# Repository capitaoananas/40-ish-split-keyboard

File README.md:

# Split-Keyboard-PCB
A 40% ish reversible split keyboard inspired by the [MiniDox](https://github.com/That-Canadian/MiniDox_PCB) keyboard

## PCB

Here's my PCB! It was made in KiCad..

### Schematic

### PCB

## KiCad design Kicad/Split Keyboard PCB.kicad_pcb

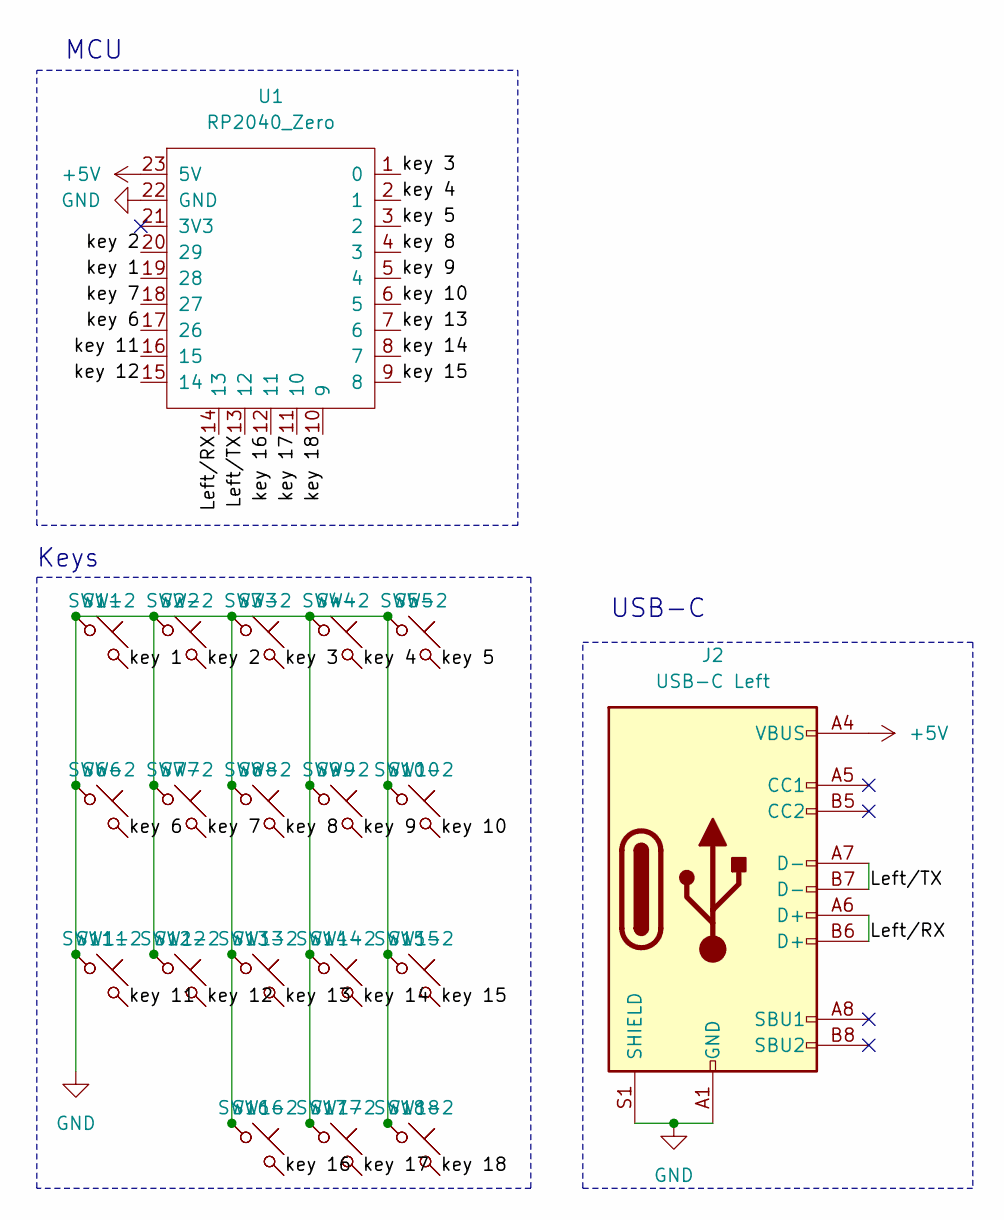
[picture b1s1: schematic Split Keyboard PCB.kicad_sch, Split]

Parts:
J2: USB-C Left; TYPE-C-31-M-13C
SW1, SW1-2, SW2, SW2-2, SW3, SW3-2, SW4, SW4-2, SW5, SW5-2, SW6, SW6-2, SW7, SW7-2, SW8, SW8-2, SW9, SW9-2, SW10, SW10-2, SW11, SW11-2, SW12, SW12-2, SW13, SW13-2, SW14, SW14-2, SW15, SW15-2, SW16, SW16-2, SW17, SW17-2: SW_Push_45deg; MX-Hotswap-1U
SW18, SW18-2: SW_Push_45deg; MX-Hotswap-1.5U
U1: RP2040_Zero

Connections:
+5V: J2.A4 (VBUS), J2.A9 (VBUS), J2.B4 (VBUS), J2.B9 (VBUS), U1.23 (5V)
/Left/RX: J2.A6 (D+), J2.B6 (D+), U1.14 (13)
/Left/TX: J2.A7 (D-), J2.B7 (D-), U1.13 (12)
/key 1: SW1.2, SW1-2.2, U1.19 (28)
/key 2: SW2.2, SW2-2.2, U1.20 (29)
/key 3: SW3.2, SW3-2.2, U1.1 (0)
/key 4: SW4.2, SW4-2.2, U1.2 (1)
/key 5: SW5.2, SW5-2.2, U1.3 (2)
/key 6: SW6.2, SW6-2.2, U1.17 (26)
/key 7: SW7.2, SW7-2.2, U1.18 (27)
/key 8: SW8.2, SW8-2.2, U1.4 (3)
/key 9: SW9.2, SW9-2.2, U1.5 (4)
/key 10: SW10.2, SW10-2.2, U1.6 (5)
/key 11: SW11.2, SW11-2.2, U1.16 (15)
/key 12: SW12.2, SW12-2.2, U1.15 (14)
/key 13: SW13.2, SW13-2.2, U1.7 (6)
/key 14: SW14.2, SW14-2.2, U1.8 (7)
/key 15: SW15.2, SW15-2.2, U1.9 (8)
/key 16: SW16.2, SW16-2.2, U1.12 (11)
/key 17: SW17.2, SW17-2.2, U1.11 (10)
/key 18: SW18.2, SW18-2.2, U1.10 (9)
GND: J2.A1 (GND), J2.A12 (GND), J2.B1 (GND), J2.B12 (GND), J2.S1 (SHIELD), SW1.1, SW1-2.1, SW2.1, SW2-2.1, SW3.1, SW3-2.1, SW4.1, SW4-2.1, SW5.1, SW5-2.1, SW6.1, SW6-2.1, SW7.1, SW7-2.1, SW8.1, SW8-2.1, SW9.1, SW9-2.1, SW10.1, SW10-2.1, SW11.1, SW11-2.1, SW12.1, SW12-2.1, SW13.1, SW13-2.1, SW14.1, SW14-2.1, SW15.1, SW15-2.1, SW16.1, SW16-2.1, SW17.1, SW17-2.1, SW18.1, SW18-2.1, U1.22 (GND)

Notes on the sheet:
USB-C
Keys
MCU

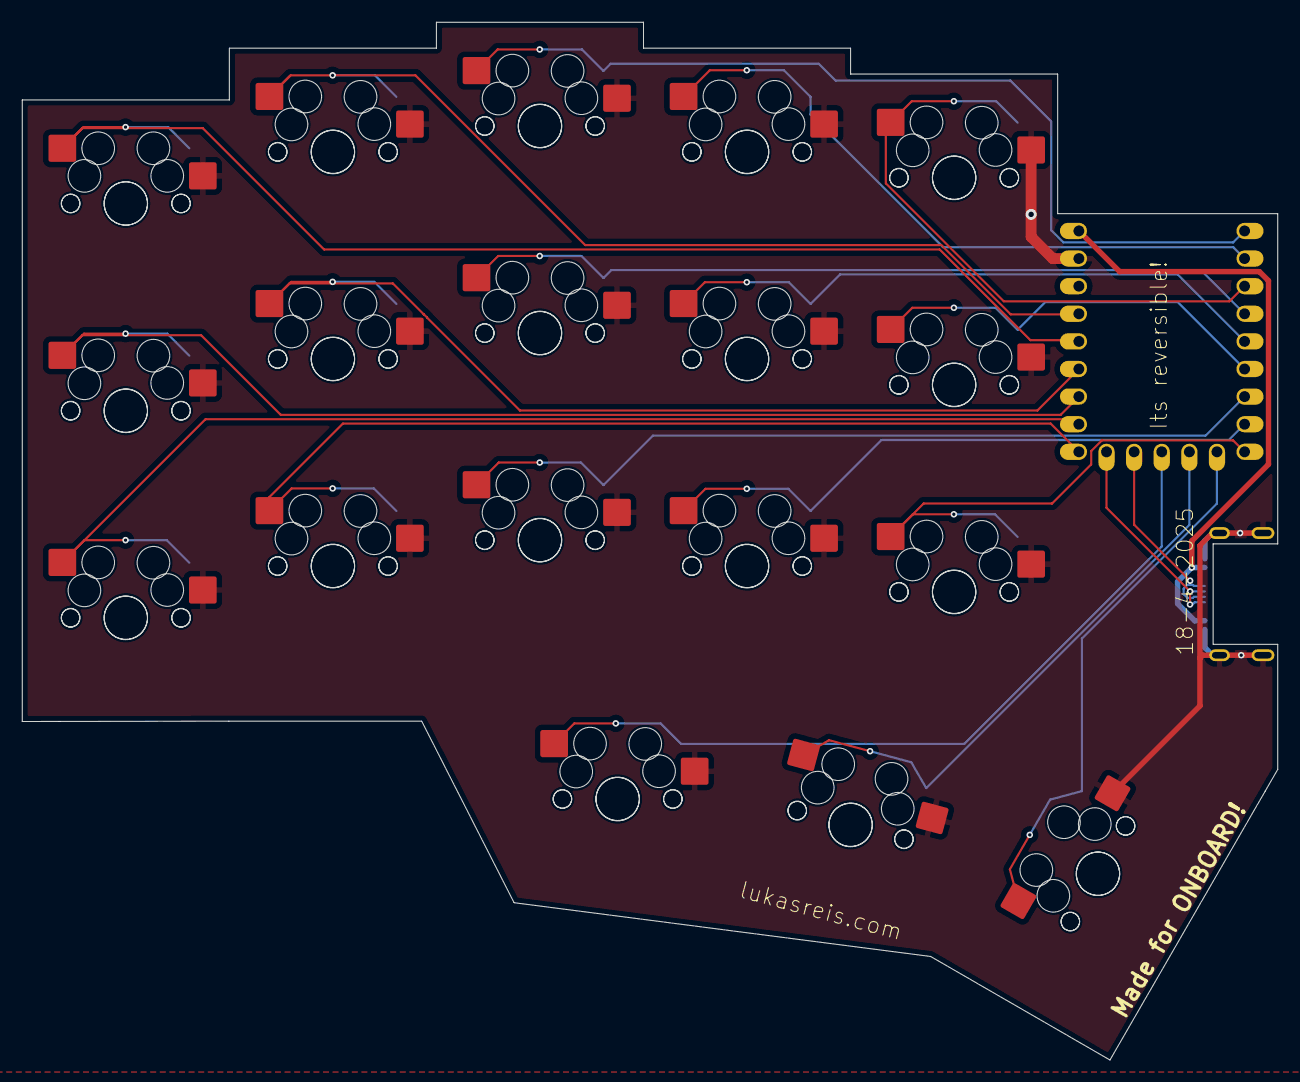
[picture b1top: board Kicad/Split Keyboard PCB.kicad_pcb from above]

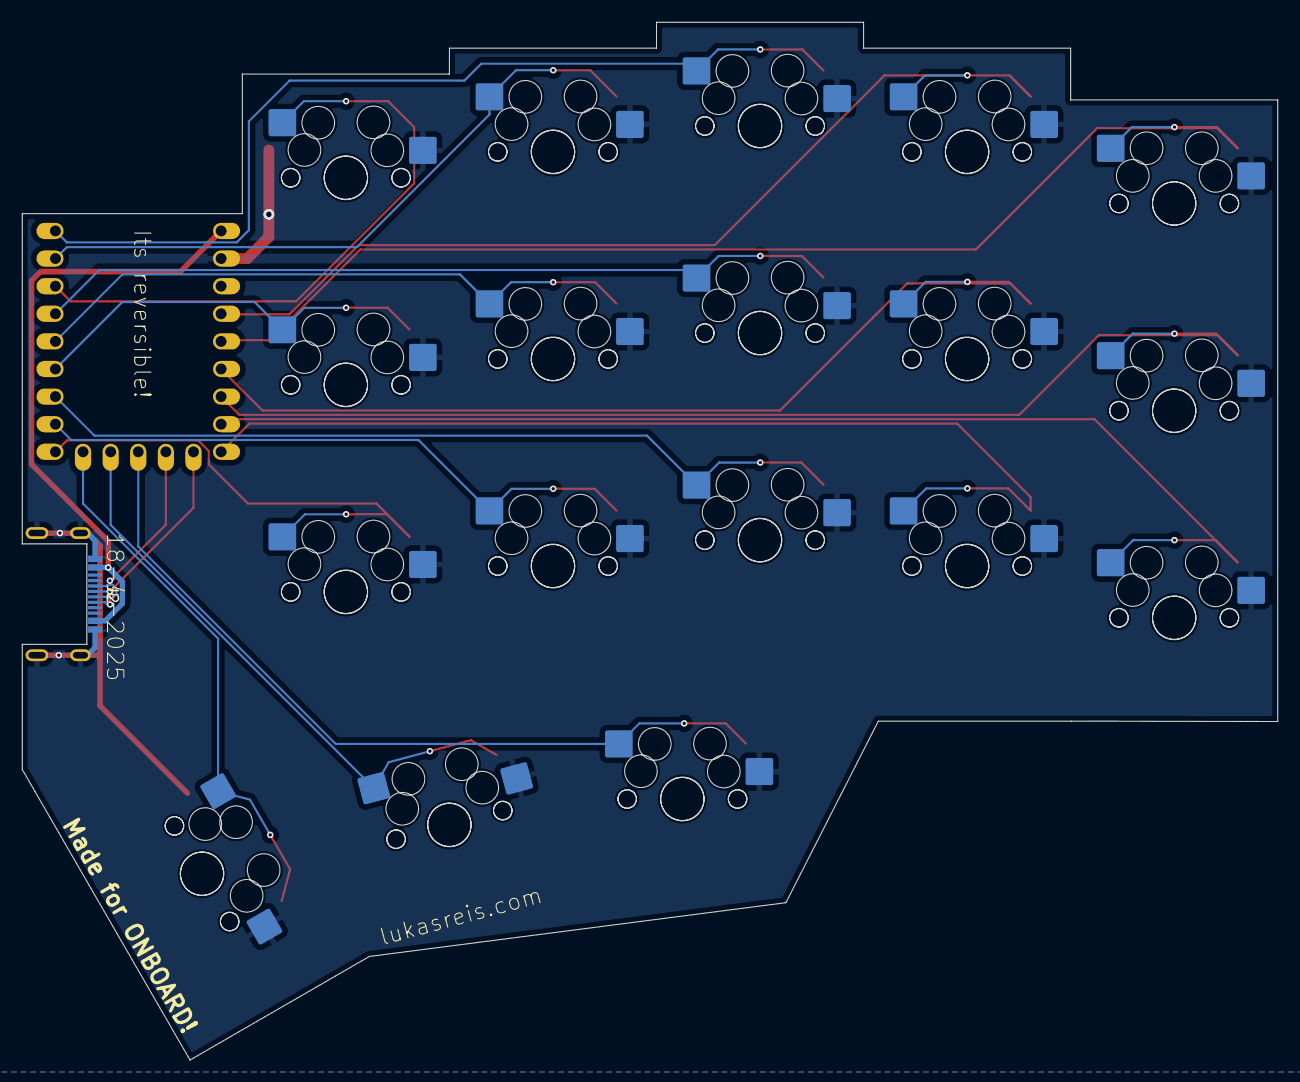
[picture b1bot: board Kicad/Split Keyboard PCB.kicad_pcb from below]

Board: 2 copper layers, 115.5 x 95.5 mm, 38 parts (19 on the bottom side), 22 nets.

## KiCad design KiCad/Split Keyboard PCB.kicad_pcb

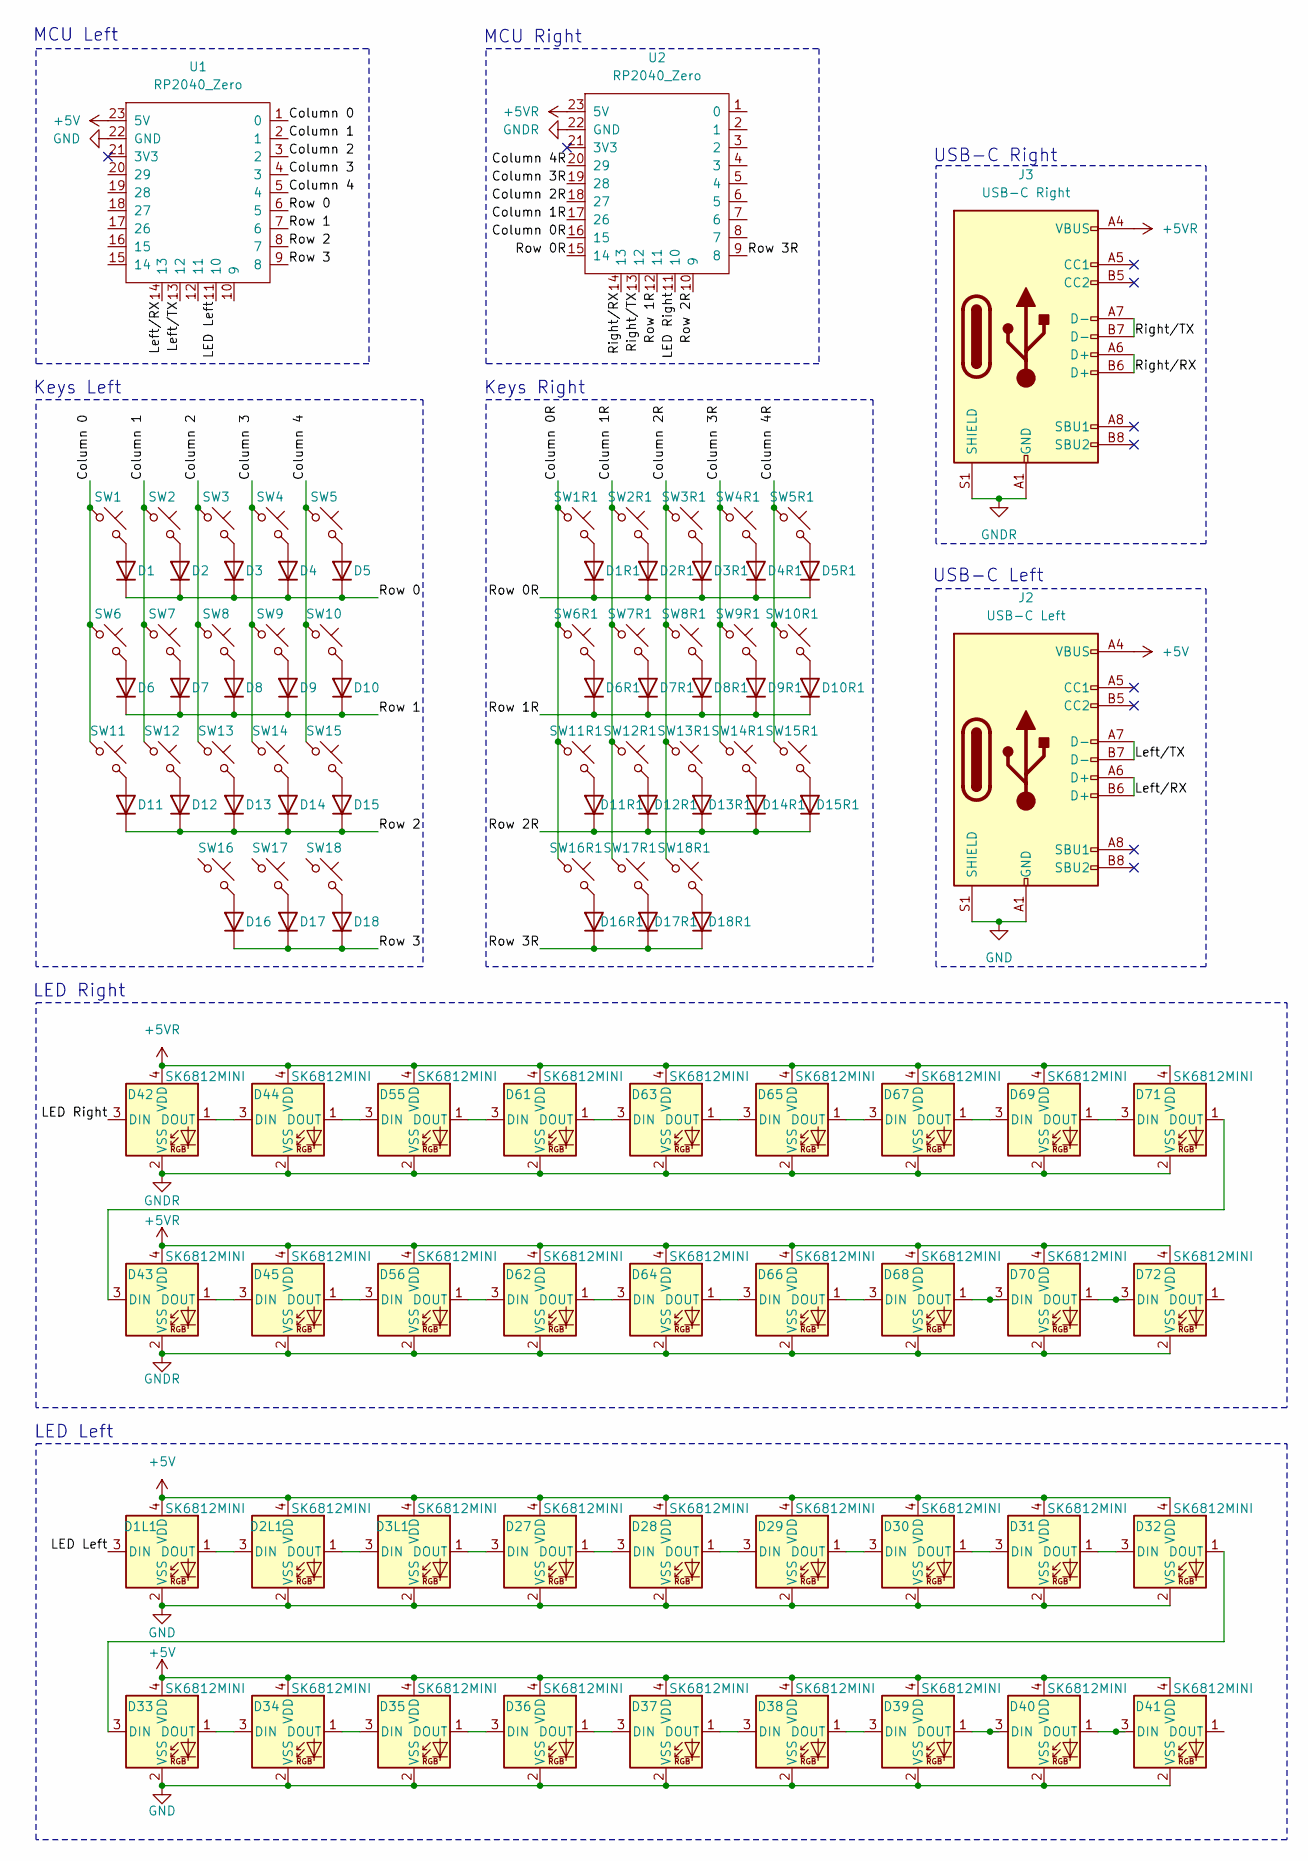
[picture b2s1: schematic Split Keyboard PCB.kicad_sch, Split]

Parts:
D1, D1R1, D2, D2R1, D3, D3R1, D4, D4R1, D5, D5R1, D6, D6R1, D7, D7R1, D8, D8R1, D9, D9R1, D10, D10R1, D11, D11R1, D12, D12R1, D13, D13R1, D14, D14R1, D15, D15R1, D16, D16R1, D17, D17R1, D18, D18R1: D; Diode_SOD-123
D1L1, D2L1, D3L1, D27, D28, D29, D30, D31, D32, D33, D34, D35, D36, D37, D38, D39, D40, D41, D42, D43, D44, D45, D55, D56, D61, D62, D63, D64, D65, D66, D67, D68, D69, D70, D71, D72: SK6812MINI; LED_SK6812MINI
J2: USB-C Left; TYPE-C-31-M-13C
J3: USB-C Right; TYPE-C-31-M-13C
SW1, SW1R1, SW2, SW2R1, SW3, SW3R1, SW4, SW4R1, SW5, SW5R1, SW6, SW6R1, SW7, SW7R1, SW8, SW8R1, SW9, SW9R1, SW10, SW10R1, SW11, SW11R1, SW12, SW12R1, SW13, SW13R1, SW14, SW14R1, SW15, SW15R1, SW16, SW17, SW17R1, SW18R1: SW_Push_45deg; MX-Hotswap-1U
SW16R1, SW18: SW_Push_45deg; MX-Hotswap-1.5U
U1, U2: RP2040_Zero

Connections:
+5V: D1L1.4 (VDD), D2L1.4 (VDD), D3L1.4 (VDD), D27.4 (VDD), D28.4 (VDD), D29.4 (VDD), D30.4 (VDD), D31.4 (VDD), D32.4 (VDD), D33.4 (VDD), D34.4 (VDD), D35.4 (VDD), D36.4 (VDD), D37.4 (VDD), D38.4 (VDD), D39.4 (VDD), D40.4 (VDD), D41.4 (VDD), J2.A4 (VBUS), J2.A9 (VBUS), J2.B4 (VBUS), J2.B9 (VBUS), U1.23 (5V)
+5VR: D42.4 (VDD), D43.4 (VDD), D44.4 (VDD), D45.4 (VDD), D55.4 (VDD), D56.4 (VDD), D61.4 (VDD), D62.4 (VDD), D63.4 (VDD), D64.4 (VDD), D65.4 (VDD), D66.4 (VDD), D67.4 (VDD), D68.4 (VDD), D69.4 (VDD), D70.4 (VDD), D71.4 (VDD), D72.4 (VDD), J3.A4 (VBUS), J3.A9 (VBUS), J3.B4 (VBUS), J3.B9 (VBUS), U2.23 (5V)
/Column 0: SW1.1, SW6.1, SW11.1, U1.1 (0)
/Column 0R: SW1R1.1, SW6R1.1, SW11R1.1, SW16R1.1, U2.16 (15)
/Column 1: SW2.1, SW7.1, SW12.1, U1.2 (1)
/Column 1R: SW2R1.1, SW7R1.1, SW12R1.1, SW17R1.1, U2.17 (26)
/Column 2: SW3.1, SW8.1, SW13.1, SW16.1, U1.3 (2)
/Column 2R: SW3R1.1, SW8R1.1, SW13R1.1, SW18R1.1, U2.18 (27)
/Column 3: SW4.1, SW9.1, SW14.1, SW17.1, U1.4 (3)
/Column 3R: SW4R1.1, SW9R1.1, SW14R1.1, U2.19 (28)
/Column 4: SW5.1, SW10.1, SW15.1, SW18.1, U1.5 (4)
/Column 4R: SW5R1.1, SW10R1.1, SW15R1.1, U2.20 (29)
/LED Left: D1L1.3 (DIN), U1.11 (10)
/LED Right: D42.3 (DIN), U2.11 (10)
/Left/RX: J2.A6 (D+), J2.B6 (D+), U1.14 (13)
/Left/TX: J2.A7 (D-), J2.B7 (D-), U1.13 (12)
/Right/RX: J3.A6 (D+), J3.B6 (D+), U2.14 (13)
/Right/TX: J3.A7 (D-), J3.B7 (D-), U2.13 (12)
/Row 0: D1.1 (K), D2.1 (K), D3.1 (K), D4.1 (K), D5.1 (K), U1.6 (5)
/Row 0R: D1R1.1 (K), D2R1.1 (K), D3R1.1 (K), D4R1.1 (K), D5R1.1 (K), U2.15 (14)
/Row 1: D6.1 (K), D7.1 (K), D8.1 (K), D9.1 (K), D10.1 (K), U1.7 (6)
/Row 1R: D6R1.1 (K), D7R1.1 (K), D8R1.1 (K), D9R1.1 (K), D10R1.1 (K), U2.12 (11)
/Row 2: D11.1 (K), D12.1 (K), D13.1 (K), D14.1 (K), D15.1 (K), U1.8 (7)
/Row 2R: D11R1.1 (K), D12R1.1 (K), D13R1.1 (K), D14R1.1 (K), D15R1.1 (K), U2.10 (9)
/Row 3: D16.1 (K), D17.1 (K), D18.1 (K), U1.9 (8)
/Row 3R: D16R1.1 (K), D17R1.1 (K), D18R1.1 (K), U2.9 (8)
GND: D1L1.2 (VSS), D2L1.2 (VSS), D3L1.2 (VSS), D27.2 (VSS), D28.2 (VSS), D29.2 (VSS), D30.2 (VSS), D31.2 (VSS), D32.2 (VSS), D33.2 (VSS), D34.2 (VSS), D35.2 (VSS), D36.2 (VSS), D37.2 (VSS), D38.2 (VSS), D39.2 (VSS), D40.2 (VSS), D41.2 (VSS), J2.A1 (GND), J2.A12 (GND), J2.B1 (GND), J2.B12 (GND), J2.S1 (SHIELD), U1.22 (GND)
GNDR: D42.2 (VSS), D43.2 (VSS), D44.2 (VSS), D45.2 (VSS), D55.2 (VSS), D56.2 (VSS), D61.2 (VSS), D62.2 (VSS), D63.2 (VSS), D64.2 (VSS), D65.2 (VSS), D66.2 (VSS), D67.2 (VSS), D68.2 (VSS), D69.2 (VSS), D70.2 (VSS), D71.2 (VSS), D72.2 (VSS), J3.A1 (GND), J3.A12 (GND), J3.B1 (GND), J3.B12 (GND), J3.S1 (SHIELD), U2.22 (GND)
unnamed: D1.2 (A), SW1.2
unnamed: D1L1.1 (DOUT), D2L1.3 (DIN)
unnamed: D1R1.2 (A), SW1R1.2
unnamed: D2.2 (A), SW2.2
unnamed: D2L1.1 (DOUT), D3L1.3 (DIN)
unnamed: D2R1.2 (A), SW2R1.2
unnamed: D3.2 (A), SW3.2
unnamed: D3R1.2 (A), SW3R1.2
unnamed: D4.2 (A), SW4.2
unnamed: D4R1.2 (A), SW4R1.2
unnamed: D5.2 (A), SW5.2
unnamed: D5R1.2 (A), SW5R1.2
unnamed: D6.2 (A), SW6.2
unnamed: D6R1.2 (A), SW6R1.2
unnamed: D7.2 (A), SW7.2
unnamed: D7R1.2 (A), SW7R1.2
unnamed: D8.2 (A), SW8.2
unnamed: D8R1.2 (A), SW8R1.2
unnamed: D9.2 (A), SW9.2
unnamed: D9R1.2 (A), SW9R1.2
unnamed: D10.2 (A), SW10.2
unnamed: D10R1.2 (A), SW10R1.2
unnamed: D11.2 (A), SW11.2
unnamed: D11R1.2 (A), SW11R1.2
unnamed: D12.2 (A), SW12.2
unnamed: D12R1.2 (A), SW12R1.2
unnamed: D13.2 (A), SW13.2
unnamed: D13R1.2 (A), SW13R1.2
unnamed: D14.2 (A), SW14.2
unnamed: D14R1.2 (A), SW14R1.2
unnamed: D15.2 (A), SW15.2
unnamed: D15R1.2 (A), SW15R1.2
unnamed: D16.2 (A), SW16.2
unnamed: D16R1.2 (A), SW16R1.2
unnamed: D17.2 (A), SW17.2
unnamed: D17R1.2 (A), SW17R1.2
unnamed: D18.2 (A), SW18.2
unnamed: D18R1.2 (A), SW18R1.2
unnamed: D3L1.1 (DOUT), D27.3 (DIN)
unnamed: D27.1 (DOUT), D28.3 (DIN)
unnamed: D28.1 (DOUT), D29.3 (DIN)
unnamed: D29.1 (DOUT), D30.3 (DIN)
unnamed: D30.1 (DOUT), D31.3 (DIN)
unnamed: D31.1 (DOUT), D32.3 (DIN)
unnamed: D32.1 (DOUT), D33.3 (DIN)
unnamed: D33.1 (DOUT), D34.3 (DIN)
unnamed: D34.1 (DOUT), D35.3 (DIN)
unnamed: D35.1 (DOUT), D36.3 (DIN)
unnamed: D36.1 (DOUT), D37.3 (DIN)
unnamed: D37.1 (DOUT), D38.3 (DIN)
unnamed: D38.1 (DOUT), D39.3 (DIN)
unnamed: D39.1 (DOUT), D40.3 (DIN)
unnamed: D40.1 (DOUT), D41.3 (DIN)
unnamed: D42.1 (DOUT), D44.3 (DIN)
unnamed: D43.3 (DIN), D71.1 (DOUT)
unnamed: D43.1 (DOUT), D45.3 (DIN)
unnamed: D44.1 (DOUT), D55.3 (DIN)
unnamed: D45.1 (DOUT), D56.3 (DIN)
unnamed: D55.1 (DOUT), D61.3 (DIN)
unnamed: D56.1 (DOUT), D62.3 (DIN)
unnamed: D61.1 (DOUT), D63.3 (DIN)
unnamed: D62.1 (DOUT), D64.3 (DIN)
unnamed: D63.1 (DOUT), D65.3 (DIN)
unnamed: D64.1 (DOUT), D66.3 (DIN)
unnamed: D65.1 (DOUT), D67.3 (DIN)
unnamed: D66.1 (DOUT), D68.3 (DIN)
unnamed: D67.1 (DOUT), D69.3 (DIN)
unnamed: D68.1 (DOUT), D70.3 (DIN)
unnamed: D69.1 (DOUT), D71.3 (DIN)
unnamed: D70.1 (DOUT), D72.3 (DIN)

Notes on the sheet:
Keys Right
LED Left
USB-C Left
MCU Right
USB-C Right
Keys Left
LED Right
MCU Left

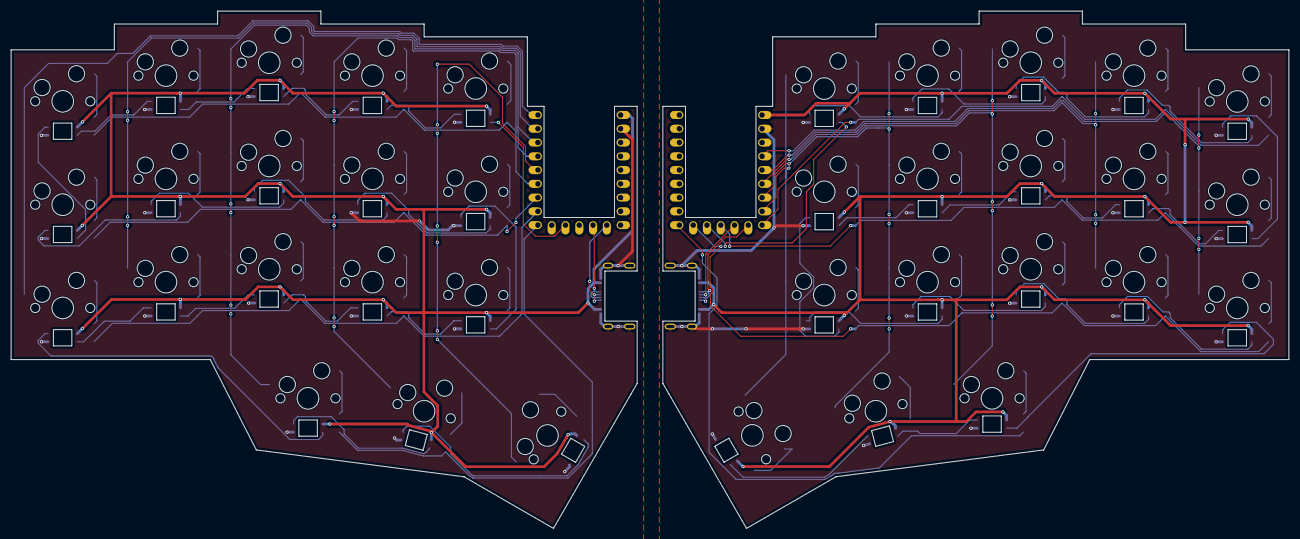
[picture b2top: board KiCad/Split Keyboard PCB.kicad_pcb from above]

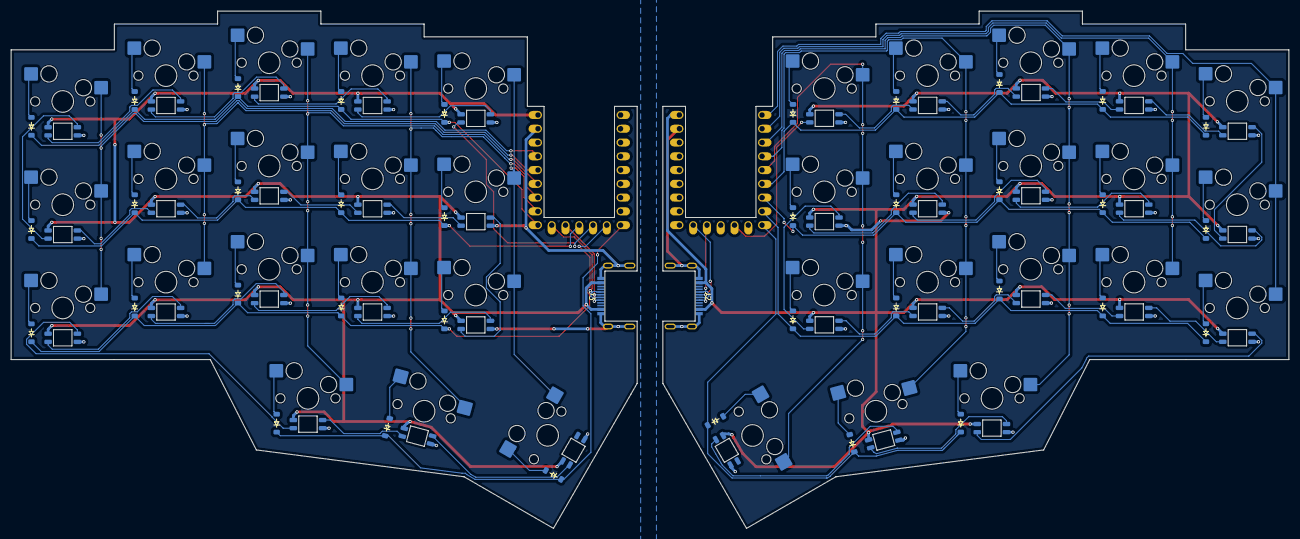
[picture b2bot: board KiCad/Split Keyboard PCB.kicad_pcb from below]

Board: 2 copper layers, 235.7 x 95.4 mm, 112 parts (112 on the bottom side), 98 nets.

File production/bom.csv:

Designator,Footprint,Quantity,Value,LCSC Part #
"D1, D10, D11, D12, D13, D14, D15, D16, D17, D18, D2, D3, D4, D5, D6, D7, D8, D9",Diode_SOD-123,18,D,
"D24, D25, D26, D27, D28, D29, D30, D31, D32, D33, D34, D35, D36, D37, D38, D39, D40, D41",LED_SK6812MINI,18,SK6812MINI,
J2,TYPE-C-31-M-13C,1,USB_C_Receptacle_USB2.0_16P,
"SW1, SW10, SW11, SW12, SW13, SW14, SW15, SW16, SW17, SW2, SW3, SW4, SW5, SW6, SW7, SW8, SW9",MX-Hotswap-1U,17,SW_Push_45deg,
SW18,MX-Hotswap-1.5U,1,SW_Push_45deg,
U1,RP2040_Zero,1,RP2040_Zero,

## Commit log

2025-04-29 add demo video
2025-05-22 add case stl files and .step file
2025-05-24 Rename actual bottom case left.stl to Bottom Left.stl
